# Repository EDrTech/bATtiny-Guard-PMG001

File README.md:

---------------------------------------------------------------------------------
> [!NOTE]
> "bATtiny Guard" and "PMG001" may be used interchangeably elsewhere in the documentation.

---------------------------------------------------------------------------------
> [!NOTE]
> <p>
> 
> Check out bATtiny Guard, now in the pre-launch stage on <a href="https://www.crowdsupply.com/edrtech/battiny-guard">CrowdSupply</a>,
> and subscribe to be notified when it’s available. 
><br clear="right"/>
></p>

---------------------------------------------------------------------------------
# bATtiny Guard Power management module

bATtiny Guard is a highly integrated module designed for efficient management of single-cell
Li-Po battery systems. It incorporates various essential ICs to address all aspects of power
management, including battery charging, switch/button power on/off behavior, undervoltage
and overvoltage protection, flexible voltage measurement, battery current measurement, and
temperature monitoring. Additionally, it features a microcontroller for programming custom
behaviors, ensuring comprehensive management of single-cell rechargeable battery
systems.
Furthermore, when paired with the demo kit base PCB, the module serves as a general
development board for the ATTINY1616, with all
18 GPIO pins accessible for any application.
&nbsp;
&nbsp;
&nbsp;
&nbsp;
&nbsp;
&nbsp;
&nbsp;
&nbsp;
&nbsp;
&nbsp;

# Features
&nbsp;
&nbsp;
&nbsp;

&nbsp;
&nbsp;
&nbsp;
&nbsp;
&nbsp;
<p>

- 32 PIN 22.22mm *16.51mm package
- On/off behavior control
- 2A single cell charger
- Single li-po cell powered
- 4+16 ADC channels
- Battery current measurement
- Brown-out detection/reset circuit
- Low on-resistance battery output MOSFET
- On-module temperature measurement
- I2C Interface
- Arduino compatible

<br clear="right"/>
</p>

---------------------------------------------------------------------------------
<p align="left">

</p>

---------------------------------------------------------------------------------
<p align="left">

</p>

---------------------------------------------------------------------------------

# Installation and set up

To program this module you will need the following:

- Arduino IDE (Or other IDE of your choosing)
- [megaTinyCore](https://github.com/SpenceKonde/megaTinyCore)
- Demo kit with the module soldered on

&nbsp;
&nbsp;
&nbsp;
&nbsp;
<p align="center">
Demo board and cover board views.
</p>
<p align="center">

</img>
</p>
&nbsp;
&nbsp;
&nbsp;
&nbsp;
&nbsp;
&nbsp;
&nbsp;
&nbsp;

There's no need to install any additional libraries as the example code only uses the wire library to handle I2C, the rest is in the [example](bATtiny_guard_default_code/bATtiny_guard_default_code.ino) code. Keep in mind that some register values are hardcoded, which is not the best way to handle something like that but is done here for the sake of simplicity. You can use external libraries with this module without issues, you just need to redefine I2C adresses of devices as they don't necessarily match with other libraries.

&nbsp;
&nbsp;
&nbsp;
&nbsp;

<p align="center">
Board settings should be set up like this:
</p>
<p align="center">

</img>
</p>

Default code provides basic power management and monitoring - press PWR_SW for >500ms and BAT_OUT will turn on, hold PWR_SW for >3s and BAT_OUT will turn off.

To start, you should have the demo board connected via USB to your computer. Powering over USB only will work most of the time, but it is strongly recommended to have the battery connected to the demo board/module.
Switching between USB modes is done with the use of a tactile switch on the demo board; for flashing/programming, set it to 'UPDI', by pressing the button again, the mode is toggled to 'Serial' which will allow for serial communication.
<p align="center">

</img>
&nbsp;
&nbsp;
&nbsp;
&nbsp;

</img>
</p>
&nbsp;
&nbsp;
&nbsp;
&nbsp;
&nbsp;
&nbsp;
&nbsp;
&nbsp;
<p align="center">
Example output to serial (ADC pins floating):
</p>
<p align="center">

</img>
</p>

For more information, please read the [datasheet](bATtiny_guard_datasheet.pdf).

---------------------------------------------------------------------------------
    
# Module Schematic

---------------------------------------------------------------------------------

# Demo board Schematic

---------------------------------------------------------------------------------
# bATtiny Series

---------------------------------------------------------------------------------
# [License](LICENSE)

<p align="left">

</p>

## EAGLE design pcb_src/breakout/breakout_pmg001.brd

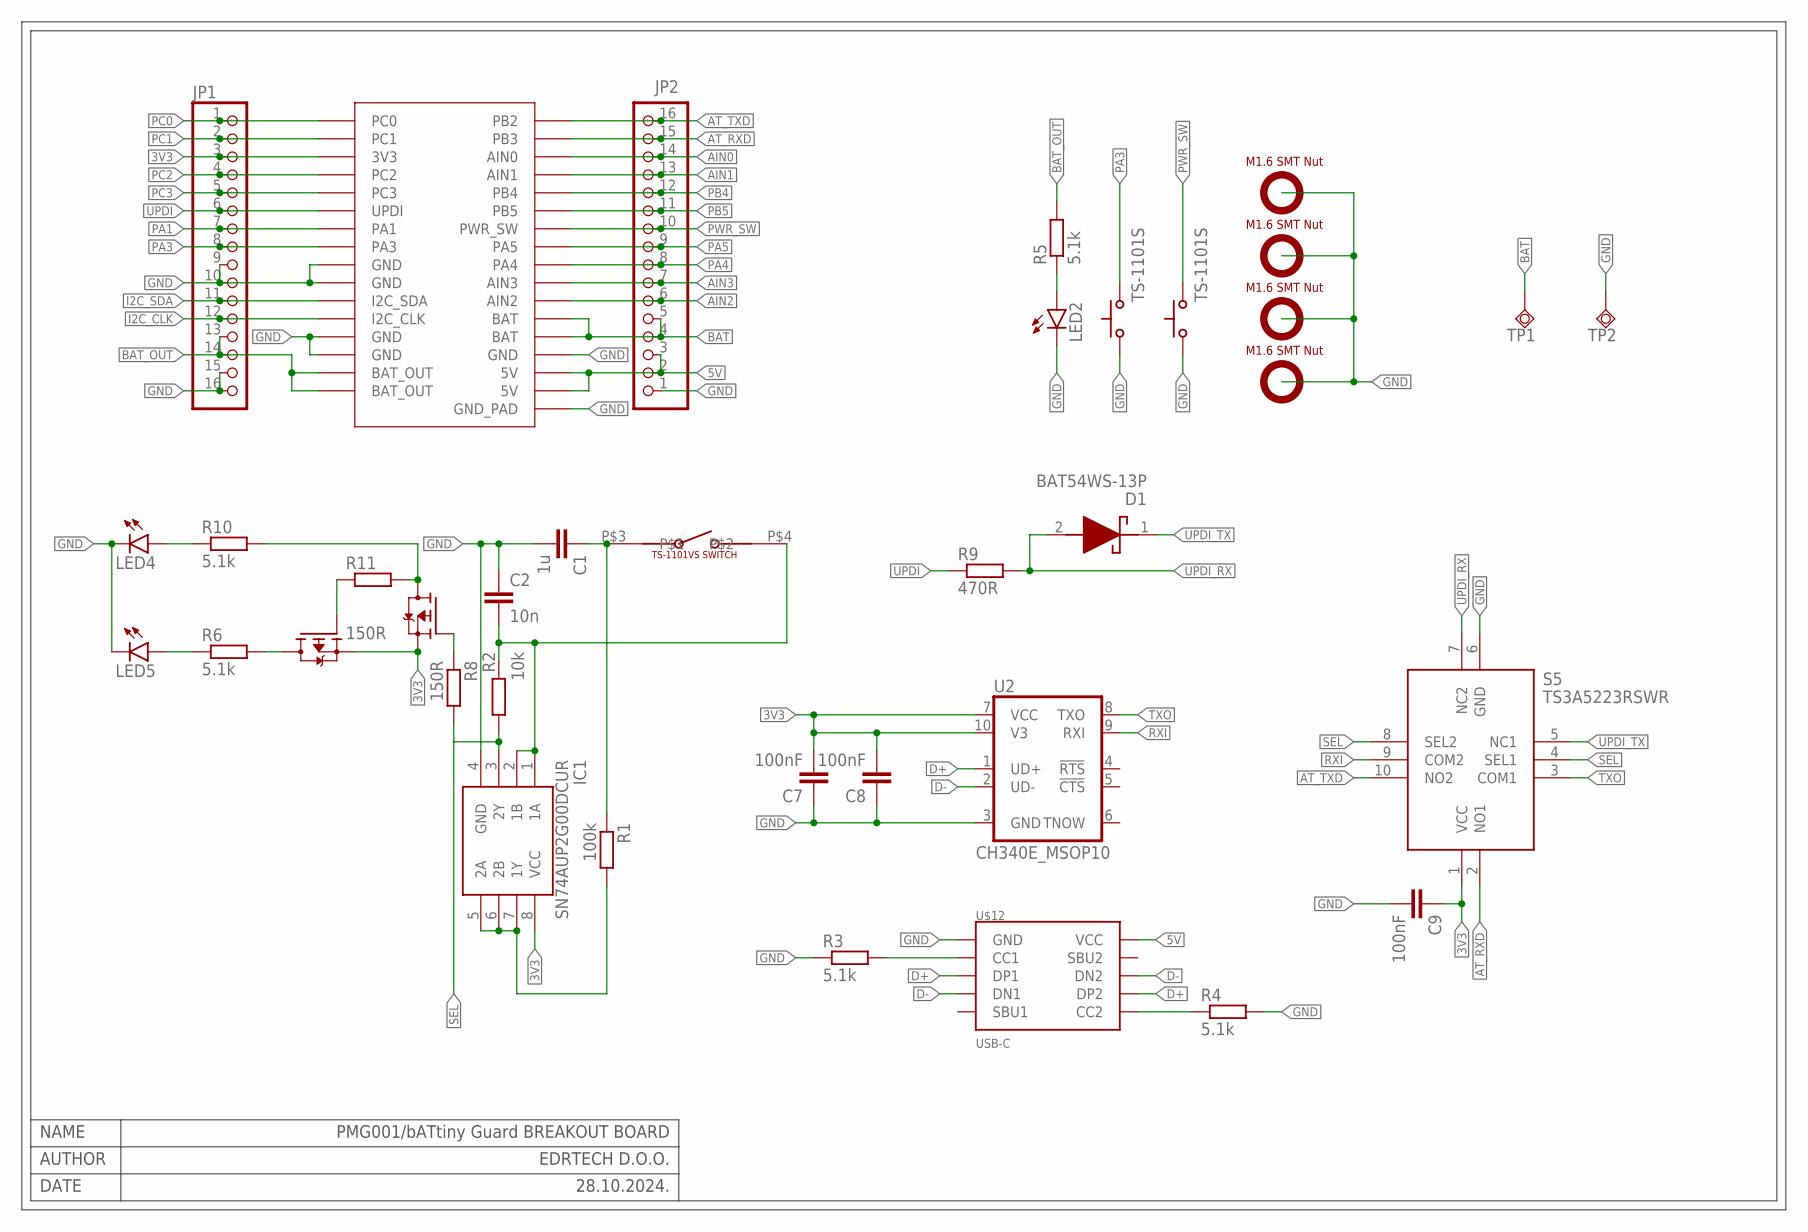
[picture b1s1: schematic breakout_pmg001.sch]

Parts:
C1: 1u; C0402
C2: 10n; C0402
C7, C8, C9: 100nF; C0402
D1: BAT54WS-13P; SOD2512X115N
IC1: SN74AUP2G00DCUR; SOP50P310X90-8N
JP1, JP2: PINHD-1X16; 1X16
LED2, LED4, LED5: LEDCHIP-LED0603; CHIP-LED0603
Q1, Q2: NTK3139PT1G; SOTFL40P120X55-3N
R1: 100k; R0402
R2: 10k; R0402
R3, R4, R5, R6, R10: 5.1k; R0402
R8, R11: 150R; R0402
R9: 470R; R0402
S5: TS3A5223RSWR; RSW(RPUQFNN10)
TP1, TP2: TPSQTP19SQ; TP19SQ
U2: CH340E_MSOP10; MSOP10
U$1, U$4: TS-1101S
U$2: TS-1101VS-C-A-A
U$7: PMG001
U$8, U$9, U$10, U$11: SMTSO16
U$12: USB-C

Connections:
3V3: C7.2, C8.2, C9.1, IC1.8 (VCC), JP1.3, Q1.2 (S), Q2.2 (S), S5.1 (VCC), U2.7 (VCC), U2.10 (V3), U$7.P$3 (3V3)
5V: JP2.2, JP2.3, U$7.P$17 (5V), U$7.P$18 (5V), U$12.VCC@1 (VCC), U$12.VCC@2 (VCC)
AIN0: JP2.14, U$7.P$30 (AIN0)
AIN1: JP2.13, U$7.P$29 (AIN1)
AIN2: JP2.6, U$7.P$22 (AIN2)
AIN3: JP2.7, U$7.P$23 (AIN3)
AT_RXD: JP2.15, S5.2 (NO1), U$7.P$31 (PB3)
AT_TXD: JP2.16, S5.10 (NO2), U$7.P$32 (PB2)
BAT: JP2.4, JP2.5, TP1.TP, U$7.P$20 (BAT), U$7.P$21 (BAT)
BAT_OUT: JP1.13, JP1.14, R5.2, U$7.P$15 (BAT_OUT), U$7.P$16 (BAT_OUT)
D+: U2.1 (UD+), U$12.DP1, U$12.DP2
D-: U2.2 (UD-), U$12.DN1, U$12.DN2
GND: C1.2, C2.1, C7.1, C8.1, C9.2, IC1.4 (GND), JP1.9, JP1.10, JP1.15, JP1.16, JP2.1, LED2.C, LED4.C, LED5.C, R3.1, R4.2, S5.6 (GND), TP2.TP, U2.3 (GND), U$1.P$1 (1), U$4.P$1 (1), U$7.P$9 (GND), U$7.P$10 (GND), U$7.P$13 (GND), U$7.P$14 (GND), U$7.P$19 (GND), U$7.P$33 (GND_PAD), U$8.P$1, U$9.P$1, U$10.P$1, U$11.P$1, U$12.GND@1 (GND), U$12.GND@2 (GND), U$12.P$1 (GND), U$12.P$2 (GND), U$12.P$3 (GND), U$12.P$4 (GND)
I2C_CLK: JP1.12, U$7.P$12 (I2C_CLK)
I2C_SDA: JP1.11, U$7.P$11 (I2C_SDA)
unnamed: C2.2, IC1.1 (1A), IC1.2 (1B), R2.1, U$2.P$4
unnamed: R3.2, U$12.CC1
unnamed: LED2.A, R5.1
unnamed: LED5.A, R6.1
unnamed: Q1.1 (G), R8.1
unnamed: R4.1, U$12.CC2
unnamed: IC1.5 (2A), IC1.6 (2B), IC1.7 (1Y), R1.2
unnamed: Q1.3 (D), R10.2, R11.2
unnamed: Q2.3 (D), R6.2
unnamed: LED4.A, R10.1
unnamed: C1.1, R1.1, U$2.P$3
unnamed: Q2.1 (G), R11.1
PA1: JP1.7, U$7.P$7 (PA1)
PA3: JP1.8, U$1.P$2 (2), U$7.P$8 (PA3)
PA4: JP2.8, U$7.P$24 (PA4)
PA5: JP2.9, U$7.P$25 (PA5)
PB4: JP2.12, U$7.P$28 (PB4)
PB5: JP2.11, U$7.P$27 (PB5)
PC0: JP1.1, U$7.P$1 (PC0)
PC1: JP1.2, U$7.P$2 (PC1)
PC2: JP1.4, U$7.P$4 (PC2)
PC3: JP1.5, U$7.P$5 (PC3)
PWR_SW: JP2.10, U$4.P$2 (2), U$7.P$26 (PWR_SW)
RXI: S5.9 (COM2), U2.9 (RXI)
SEL: IC1.3 (2Y), R2.2, R8.2, S5.4 (SEL1), S5.8 (SEL2)
TXO: S5.3 (COM1), U2.8 (TXO)
UPDI: JP1.6, R9.1, U$7.P$6 (UPDI)
UPDI_RX: D1.2 (A), R9.2, S5.7 (NC2)
UPDI_TX: D1.1 (K), S5.5 (NC1)

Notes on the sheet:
PMG001/bATtiny Guard BREAKOUT BOARD
NAME
AUTHOR
DATE
EDRTECH D.O.O.
28.10.2024.

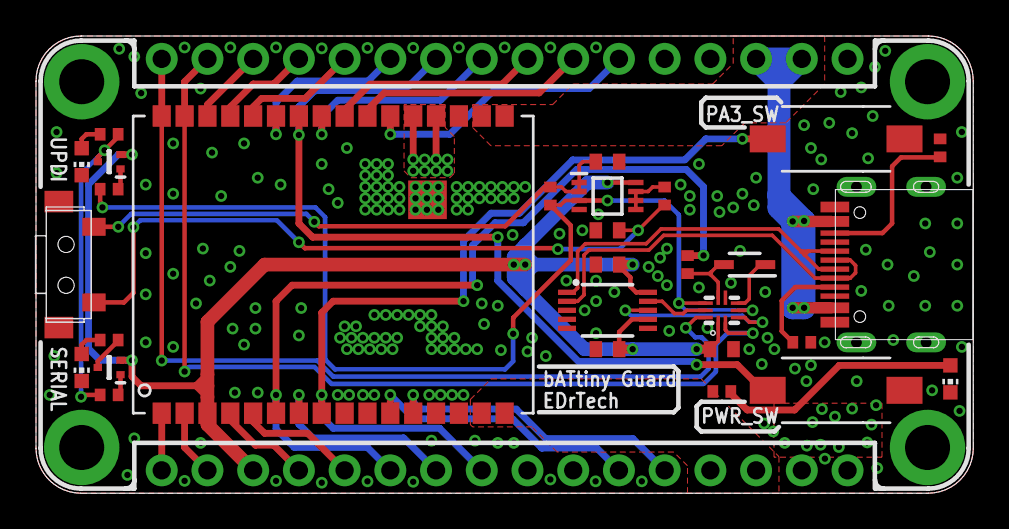
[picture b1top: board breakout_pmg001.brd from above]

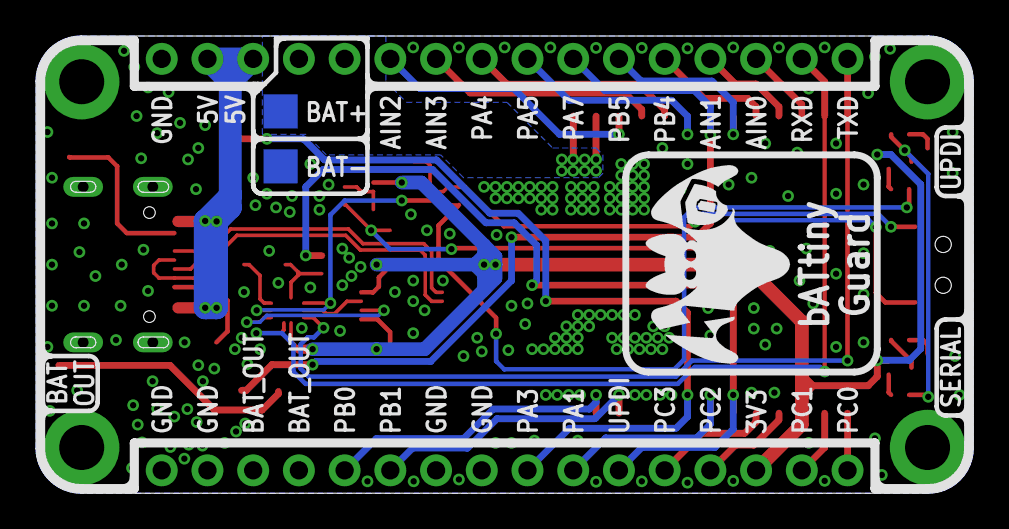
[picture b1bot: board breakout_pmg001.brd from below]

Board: 2 copper layers, 52.1 x 25.4 mm, 37 parts (2 on the bottom side), 44 nets.

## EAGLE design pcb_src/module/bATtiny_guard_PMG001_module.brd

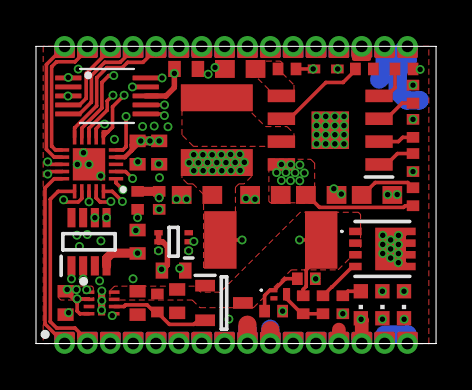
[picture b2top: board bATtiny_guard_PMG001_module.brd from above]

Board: 6 copper layers, 22.2 x 16.5 mm, 45 parts (0 on the bottom side), 43 nets.

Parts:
C1, C2, C3, C18, C43: 100nF; C0402
C28: 10uF; C0402
C35, C36, C39: 10uF; C0603
C37, C38: 22uF; C0603
C40, C41: 1uF; C0402
D15: SOD523
IC1: APX803D-29SAG-7; SOT96P240X110-3N
IC2: ATTINY1616-MNR; QFN40P300X300X90-21N
IC3: LD56100DPU30R; SON40P120X160X50-9N
IC4: IP2312; SOIC127P600X165-9N
IC5: TMP102AIDRLR; SOTFL50P160X60-6N
IC6: DMP3013SFV-7; DMP3036SFV7
IC9: INA219AIDCNR; SOP65P280X145-8N
LED1_CHRG, LED2_FULL: CHIPLED_0603
LED_BUILTIN: CHIPLED_0603
Q1: PMZ290UNE2YL
R1, R13, R14: 20K; R0402
R2, R7: 5.1k; R0402
R3: 45k; R0402
R4: 0.5R; R0402
R5: 51K; R0402
R6: 1K; R0402
R8, R10, R11: 100R; R0402
R9, R16: 150R; R0402
R12: 2R; R0402
R22: 0.01R; R2512
U1: ADS1015IDGSR; SOP50P490X110-10N
U$1, U$2: 1.27_MALE_16P_HEADER
U$91: 1uH; NRS5040T3R3NMGJ

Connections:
3V3: C2.1, C3.1, C18.1, C28.1, C41.1, C43.1, IC2.4, IC3.1, IC3.2, IC3.4, IC5.4, IC5.5, IC9.4, R2.2, R7.2, U1.8, U$2.P$14
5V: C36.1, C39.1, IC4.8, R12.1, U$1.P$15, U$1.P$16
AIN0: U1.4, U$1.P$3
AIN1: U1.5, U$1.P$4
AIN2: U1.6, U$1.P$11
AIN3: U1.7, U$1.P$10
BATTERY: C37.1, D15.C, IC9.1, R4.2, R6.2, R22.2, U$1.P$12, U$1.P$13, U$91.P$1
BAT_OUT: IC6.5, IC6.6, IC6.7, IC6.8, IC6.9, U$2.P$1, U$2.P$2
BTAP: C1.1, C40.1, IC1.3, IC3.7, IC3.8, IC6.1, IC6.2, IC6.3, IC9.2, R1.1, R14.2, R22.1
GND: C1.2, C2.2, C3.2, C18.2, C28.2, C35.2, C36.2, C37.2, C38.2, C39.2, C40.2, C41.2, C43.2, D15.A, IC1.1, IC2.3, IC2.21, IC3.3, IC3.5, IC3.9, IC4.9, IC5.2, IC9.3, IC9.7, IC9.8, LED1_CHRG.C, LED2_FULL.C, LED_BUILTIN.C, Q1.2, R3.1, R5.2, R13.1, U1.1, U1.3, U$1.P$14, U$2.P$3, U$2.P$4, U$2.P$7, U$2.P$8
I2C_CLK: IC2.14, IC5.1, IC9.5, R2.1, U1.10, U$2.P$5
I2C_SDA: IC2.13, IC5.6, IC9.6, R7.1, U1.9, U$2.P$6
LED_BUILTIN: IC2.1, R8.2
unnamed: Q1.1, R9.2, R13.2
unnamed: LED_BUILTIN.A, R8.1
unnamed: IC6.4, R16.2
unnamed: IC4.6, R3.2
unnamed: C35.1, R12.2
unnamed: LED1_CHRG.A, R10.1
unnamed: LED2_FULL.A, R11.1
unnamed: IC4.4, R5.1
unnamed: IC4.2, R6.1
unnamed: IC4.1, R10.2
unnamed: IC4.3, R11.2
unnamed: C38.1, IC4.5, R4.1
unnamed: IC4.7, U$91.P$2
PA1: IC2.20, U$2.P$10
PA3: IC2.2, U$2.P$9
PA4: IC2.5, U$1.P$9
PA5: IC2.6, U$1.P$8
PB2: IC2.12, U$1.P$1
PB3: IC2.11, U$1.P$2
PB4: IC2.10, U$1.P$5
PB5: IC2.9, U$1.P$6
PC0: IC2.15, U$2.P$16
PC1: IC2.16, U$2.P$15
PC2: IC2.17, U$2.P$13
PC3: IC2.18, U$2.P$12
PWR_SW: IC2.8, U$1.P$7
P_ON: IC2.7, R9.1
P_ON_DS: Q1.3, R14.1, R16.1
SPC_EN: IC1.2, IC3.6, R1.2
UPDI: IC2.19, U$2.P$11

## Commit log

2024-10-22 Reworked repository
    Name changed, added a lot of new resources etc.
2024-10-22 Updated schematic
    Updated to last version.
2024-10-29 Updated to latest revision
    Documentation updated to match the latest hardware revision.
2024-10-29 Added photos
2024-10-29 Added photo
2024-10-29 Updated image
2024-10-29 Added banner
2024-10-29 Added image
2024-10-29 Updated images
2024-11-01 Added OSHW Certification badge
2024-11-01 Added OSHW Certification badge
    Added to license paragraph of readme
2024-11-16 Added breadboard and board holder
    Added laser cut files for a breadboard and demo board for easy integration.
